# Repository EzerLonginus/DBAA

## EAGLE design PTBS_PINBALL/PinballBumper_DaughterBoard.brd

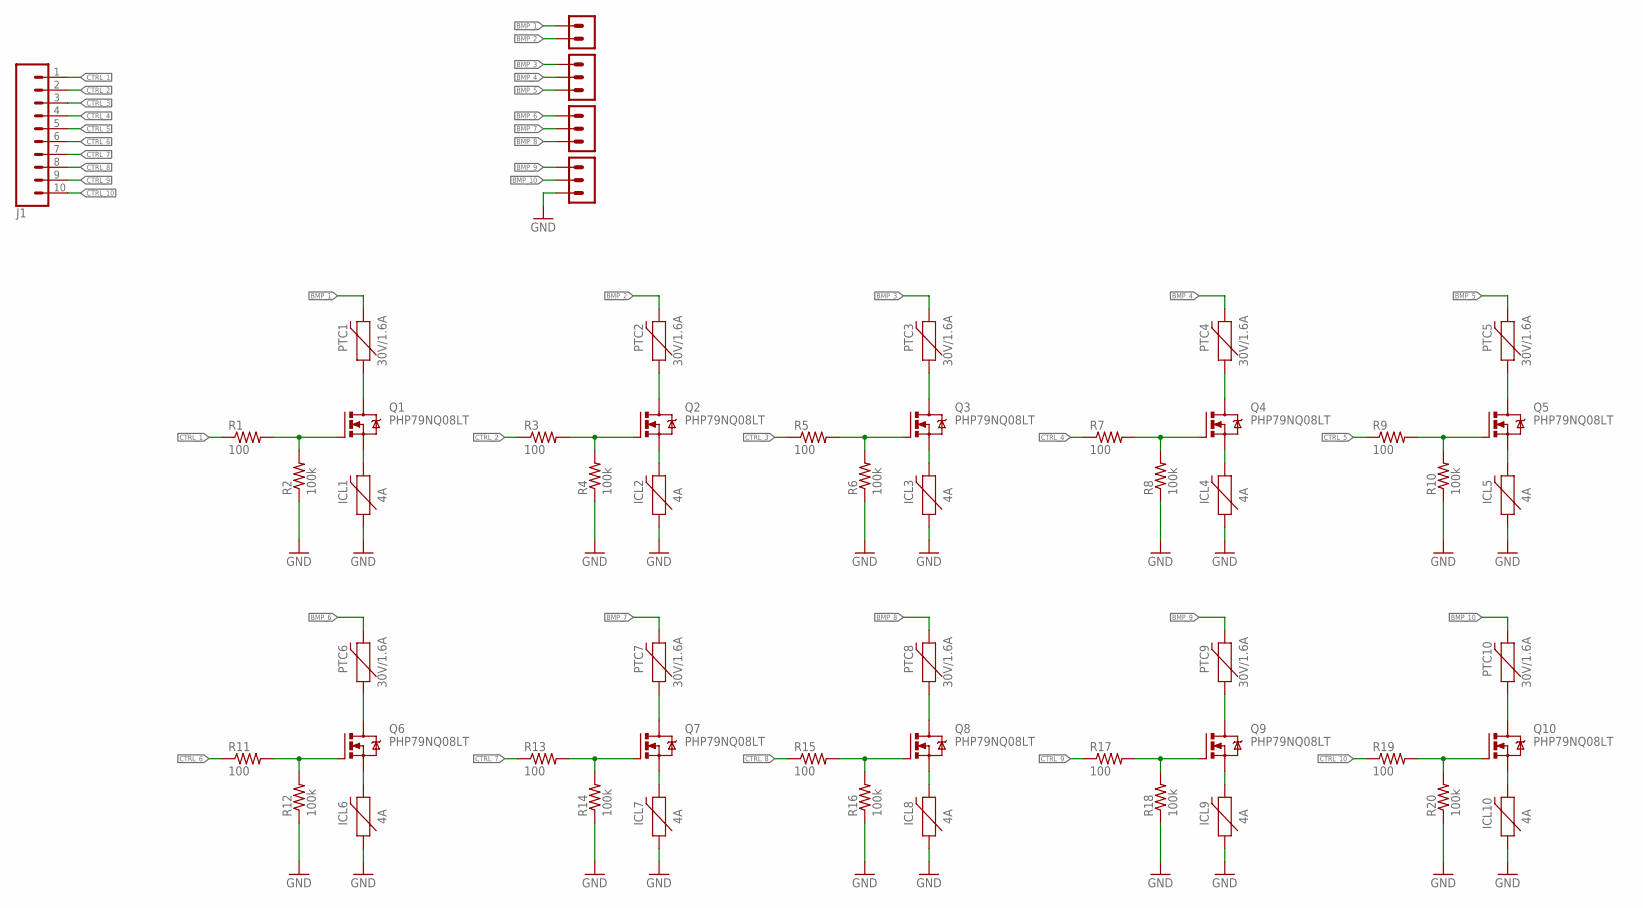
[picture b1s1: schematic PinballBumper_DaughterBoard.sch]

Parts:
ICL1, ICL2, ICL3, ICL4, ICL5, ICL6, ICL7, ICL8, ICL9, ICL10: 4A; PTH
J1: CONN_10"; 1X10
PTC1, PTC2, PTC3, PTC4, PTC5, PTC6, PTC7, PTC8, PTC9, PTC10: 30V/1.6A; PTH
Q1, Q2, Q3, Q4, Q5, Q6, Q7, Q8, Q9, Q10: PHP79NQ08LT; TO220BV
R1, R3, R5, R7, R9, R11, R13, R15, R17, R19: 100; 0204/7
R2, R4, R6, R8, R10, R12, R14, R16, R18, R20: 100k; 0204/7
U$1: BIG_TERMINAL_2PINBIG; BIG_TERMINAL_2PIN
U$2, U$3, U$4: BIG_TERMINAL_3PINBIG; BIG_TERMINAL_3PIN

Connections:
BMP_1: PTC1.P$2 (2), U$1.P$1
BMP_2: PTC2.P$2 (2), U$1.P$2
BMP_3: PTC3.P$2 (2), U$2.1
BMP_4: PTC4.P$2 (2), U$2.2
BMP_5: PTC5.P$2 (2), U$2.3
BMP_6: PTC6.P$2 (2), U$3.1
BMP_7: PTC7.P$2 (2), U$3.2
BMP_8: PTC8.P$2 (2), U$3.3
BMP_9: PTC9.P$2 (2), U$4.1
BMP_10: PTC10.P$2 (2), U$4.2
CTRL_1: J1.1, R1.1
CTRL_2: J1.2, R3.1
CTRL_3: J1.3, R5.1
CTRL_4: J1.4, R7.1
CTRL_5: J1.5, R9.1
CTRL_6: J1.6, R11.1
CTRL_7: J1.7, R13.1
CTRL_8: J1.8, R15.1
CTRL_9: J1.9, R17.1
CTRL_10: J1.10, R19.1
GND: ICL1.P$1 (1), ICL2.P$1 (1), ICL3.P$1 (1), ICL4.P$1 (1), ICL5.P$1 (1), ICL6.P$1 (1), ICL7.P$1 (1), ICL8.P$1 (1), ICL9.P$1 (1), ICL10.P$1 (1), R2.1, R4.1, R6.1, R8.1, R10.1, R12.1, R14.1, R16.1, R18.1, R20.1, U$4.3
unnamed: PTC1.P$1 (1), Q1.D
unnamed: Q1.G, R1.2, R2.2
unnamed: ICL1.P$2 (2), Q1.S
unnamed: PTC2.P$1 (1), Q2.D
unnamed: Q2.G, R3.2, R4.2
unnamed: ICL2.P$2 (2), Q2.S
unnamed: PTC3.P$1 (1), Q3.D
unnamed: Q3.G, R5.2, R6.2
unnamed: ICL3.P$2 (2), Q3.S
unnamed: PTC4.P$1 (1), Q4.D
unnamed: Q4.G, R7.2, R8.2
unnamed: ICL4.P$2 (2), Q4.S
unnamed: PTC5.P$1 (1), Q5.D
unnamed: Q5.G, R9.2, R10.2
unnamed: ICL5.P$2 (2), Q5.S
unnamed: PTC6.P$1 (1), Q6.D
unnamed: Q6.G, R11.2, R12.2
unnamed: ICL6.P$2 (2), Q6.S
unnamed: PTC7.P$1 (1), Q7.D
unnamed: Q7.G, R13.2, R14.2
unnamed: ICL7.P$2 (2), Q7.S
unnamed: PTC8.P$1 (1), Q8.D
unnamed: Q8.G, R15.2, R16.2
unnamed: ICL8.P$2 (2), Q8.S
unnamed: PTC9.P$1 (1), Q9.D
unnamed: Q9.G, R17.2, R18.2
unnamed: ICL9.P$2 (2), Q9.S
unnamed: PTC10.P$1 (1), Q10.D
unnamed: Q10.G, R19.2, R20.2
unnamed: ICL10.P$2 (2), Q10.S

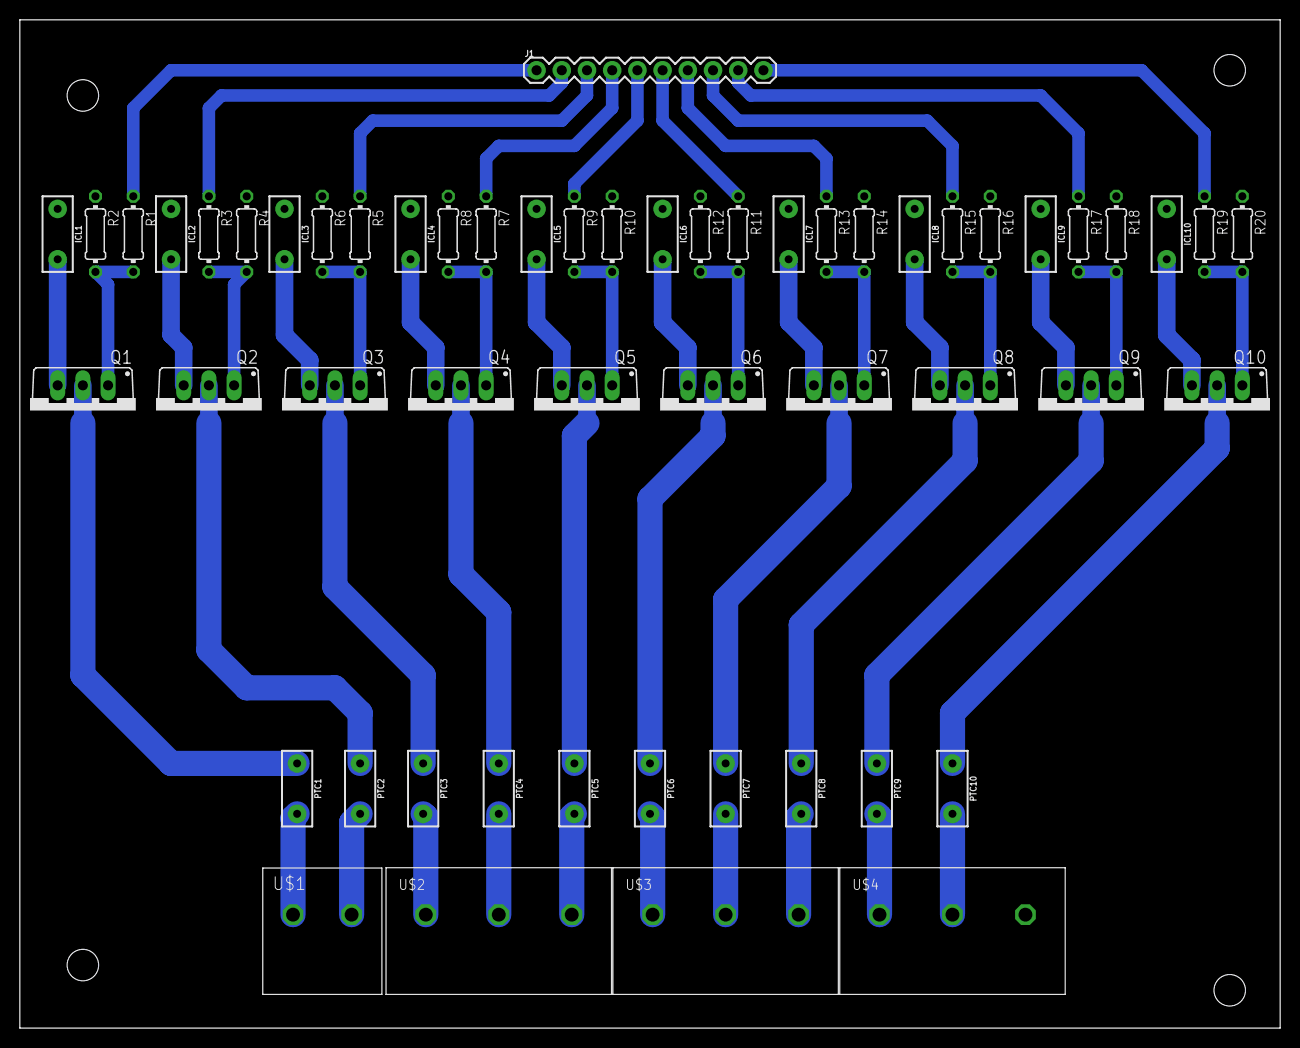
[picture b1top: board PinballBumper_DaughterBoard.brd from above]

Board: 2 copper layers, 127.0 x 101.6 mm, 55 parts (0 on the bottom side), 51 nets.

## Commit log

2018-12-29 BumperControl_DaughterBoard
    Eagle Schematic and Layout for the Bumper Control Daughter Board
2018-12-31 Relay Tester Board
    Relay Tester for Solenoid Board. Teensy or Switching Control.

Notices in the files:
parts and their libraries:
SparkFun-Fuses: Licensing: Creative Commons ShareAlike 4.0 International - https://creativecommons.org/licenses/by-sa/4.0
